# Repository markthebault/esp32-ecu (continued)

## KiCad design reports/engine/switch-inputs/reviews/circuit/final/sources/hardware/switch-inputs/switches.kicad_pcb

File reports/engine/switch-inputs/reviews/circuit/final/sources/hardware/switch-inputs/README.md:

# SW2-J4-DRAFT1 switch accessory

Separate80×60mm, two-layer, direct-solder THT prototype for two secondary-table dry contacts. The120×120mm carrier, service buttons, SAFE_N and archived manufacturing/case files retain their existing roles. **HOLD: no fabrication release, electrical rating, enclosure-fit or engine qualification.**

[Native schematic](switches.kicad_sch), [routed PCB](switches.kicad_pcb), [literal contract](net_contract.json) and [candidate BOM](bom.csv) describe42 footprints:38 fitted parts and four unplated M3 mounts. U1 is a directly soldered MCP23008-E/P PDIP18, without a socket. Ordinary resistors stand upright; confirm formed-lead and body heights before assembly. Exact capacitors, contact parts, wire/glands, mounting materials and some procurement choices remain open.

## Connections and ownership

| Carrier J4 | Accessory J1, XH4 | Signal |
| --- | --- | --- |
|1|1|GND|
|2|2|3V3|
|3|3|SDA, GPIO41|
|4|4|SCL, GPIO42|
|5|No wire or contact|SAFE_N, never connect to this accessory|

J4 is an internal3.3V logic header. Use a short internal harness with a five-position carrier housing and only positions1..4 populated, adapting to J1’s XH4 housing. The exact2.54mm carrier housing/contact and retention must be checked against the actual header. No loose fifth lead is permitted. J1 uses XHP-4 and four SXH-001T-P0.6 contacts as candidates; wire gauge/crimp tooling and fit need checking.

External J2 and J3 are VH2 connectors with3.96mm pitch, deliberately different from internal J1’s2.50mm XH4. Each VH2 uses pin1 SW and pin2 its ground return; J2 is input0 and J3 input1. VHR-2N housings and four SVH-21T-P1.1 contacts are candidates, with wire/crimp/retention checks pending. Keep these connectors inside the box and route each external pair through an appropriately selected sealed cable exit. No new sealed-box or printed-fit qualification is implied. Use dry-circuit rated switch contacts for the small sensing current.

A contact closes SW to its dedicated return. **Closed reads high, open reads low**, after transistor inversion. Selection polarity remains configurable per rule. An open wire looks open; a short to return looks closed. Static external voltage faults may also look like valid contact states. No continuity or wrong-wire diagnosis is implemented.

Saving a secondary rule in Input mode explicitly reserves J4’s bus and address0x20 for this fixed accessory contract. Connect no other I2C owner/device there. The marker/loop checks establish behavior, not unique identity. With neither rule in Input mode the firmware makes no device/register requests and releases its owned peripheral handles. PAIR, RESET, cam, pressure and SAFE_N retain their existing functions.

## Circuit and bounds

Each channel uses a1N4148 feed diode and2.2k0.6W1% bias, two4.99k1% base resistors,100k base-emitter bias, a reverse-BE1N4148 clamp, onsemi2N3904BU,4.7k collector pullup,10nF filtering and1k isolation to GP0/GP1. Do not substitute a transistor with another E/B/C bondout. GP2..5 have10k straps for0x28 under mask0x3C. GP7 is output-only on MCP23008; it drives GP6 through1k, with100k GP6 pulldown. These resistors limit contention if a register changes; they do not diagnose every contact failure.

MCP121-300E/TO is the prototype reset supervisor, with100k pullup matching its published test condition, local100nF bypass and a mandatory1k rail bleeder. The static trip range is2.857..3.003V; the stated80..180ms release interval has specified test conditions. Reset output leakage has no published maximum, hysteresis limits are at25°C, and assertion delay is typical only. The assembled RESET high/low margins, arbitrary ramps, power interruption and behavior below the specified operating supply remain unqualified. No guaranteed deep-brownout assertion is inferred from a different output load.

The feed diodes do not eliminate backfeed. Transistor B-C junctions and I2C/input clamp paths can energize an unpowered local rail. The1k bleeder and100Ω SDA/SCL series resistors are part of the prototype, not proof of safe arbitrary power sequences. The carrier already has4.7k I2C pullups; add no further bus pullups. Use100kHz and measure actual rise time/capacitance, VOL and fault behavior with the finished harness. Digital marker/loop/readback checks do not validate the analog conditioners: wrong transistor orientation, clamp faults or external wiring may still produce plausible contact bits. Independently measure both channels’ voltages/currents before accepting their raw levels.

The carrier LD1117’s200mA figure is a provisional **total thermal target**, not available accessory headroom. Measure the complete carrier, ESP32/Wi-Fi peaks and accessory rail loading/temperature. The module5V pad21 is NC. [Existing USB power restrictions](../../docs/web-configuration.md) still apply: remove the unpowered module before USB power; never combine powered carrier3V3 and module USB. A removed USB-powered module cannot read carrier sensors/J4.

MCP23008’s E order code does not establish3.3V operation to125°C. The data sheet’s3.3V operating domain ends at85°C. No assembled temperature rating is established. MRS25 candidate order codes are derived from the manufacturer’s coding scheme;0.6W is P70 subject to film/ambient limits, not an unrestricted enclosure dissipation rating. Exact capacitor part/body/lead spacing and all supplier footprints require physical verification.

## Acquisition and debugging

The monitor requests one logical operation per nominal5ms iteration. Startup reads the static marker before writes, sets sequential mode, configures GP7 as output, then alternates loopback challenges. Each GPIO sample reads registers0..10 and separately rereads IODIR. Owned configuration, marker, OLAT, INTF and loopback must agree; historical INTCAP is intentionally unused. A reset before the final guard rejects. A later reset remains unobserved until the next acquisition or freshness limit.

The entire operation has a measured3ms acceptance budget in the controller’s GP-timer epoch. Each synchronous SDK transfer receives the floored remaining integer-ms timeout; the trailing guard cannot start with less than1ms remaining. Source time is acquisition start. Writes never refresh it. SDK allocation/removal and preemption have no hard3ms deadline guarantee; an elapsed overrun invalidates the sample. Actual scheduling and watchdog behavior require HIL measurement.

Bus absence/NACK/timeout, register/loop/marker mismatch, malformed replies, elapsed overrun and producer gaps invalidate required inputs. Recoverable faults back off100ms and stay latched until a completed control observation consumes that exact fault ID. Successful reads alone cannot hide a fault when the engine lock was busy. A new guarded sample and each rule’s qualification period are required after acknowledgement. Clock/state faults require an ECU restart and survive Off/Input changes. Both rules may share one sampled channel with independent polarity/debounce.

The Engine page shows acquisition phase, requested mask, current/last fault, exact decimal-string source times/counters, fault awaiting consumption, operation durations and SDK ownership/result. Per-rule qualification, pending transition, age, raw level and selection remain in the existing web/USB/MSL diagnostics. Host stimuli stay synthetic; absent hardware diagnostics stay unknown. This adds no new tune/runtime wire fields or controller identity.

Start a future bench test with outputs disconnected/inhibited and both rules Off. Check rails and J4 wiring before enabling Input. Confirm each contact’s open/closed raw level, selected polarity, debounce and fault recovery, then deliberately test absence/reset/stuck lines and source freshness. Measure protection currents, reset levels, power-off backfeed, supply loading/temperature, scheduling and USB/RF interactions. A passing software/CAD/model check does not replace these measurements.

## Reproduction and limits

`/usr/bin/python3 scripts/build_switch_inputs.py` creates a fresh draft and refuses to replace an existing board without `--replace-generated`. Routing uses `scripts/route_switch_inputs.py` with pinned Freerouting1.9.0 and analytics disabled. Native KiCad9 all-severity ERC/DRC, connectivity and schematic parity are separate checks. No Gerber, drill or enclosure release is supplied.

`tools/run_switch_circuit.py` runs95 conditional ngspice cases: assumed BJT gain/temperature/rail/contact combinations, steady±18V experiments, unpowered I2C backfeed and two transient step sizes. Powered bus pullups follow the carrier rail; disconnected-supply cases use3.3V bus, plus a separate3.63V bus-only case. Bus-feed and carrier3V3-feed currents are reported separately. Its generic transistor/diode/clamp/supervisor parameters are **not manufacturer models or physical guarantees**. The±18V experiment is not an input rating or automotive surge test. The model intentionally retains backfeed and continuity limitations. Independent component-corner arithmetic likewise does not certify saturation/cutoff outside the manufacturer’s stated test conditions.

Primary references: [MCP23008 DS20001919I](https://ww1.microchip.com/downloads/aemDocuments/documents/APID/ProductDocuments/DataSheets/MCP23008-and-MCP23008-Data-Sheet-DS20001919.pdf), [MCP121 DS20001906D](https://ww1.microchip.com/downloads/en/DeviceDoc/20001906D.pdf), [onsemi2N3904](https://www.onsemi.com/download/data-sheet/pdf/2n3904-d.pdf), [1N4148](https://www.vishay.com/docs/81857/1n4148.pdf) and [MRS25](https://www.vishay.com/docs/28724/mrs16m25.pdf). Footprint origins and omitted metadata are recorded in [provenance](footprint-provenance.json).

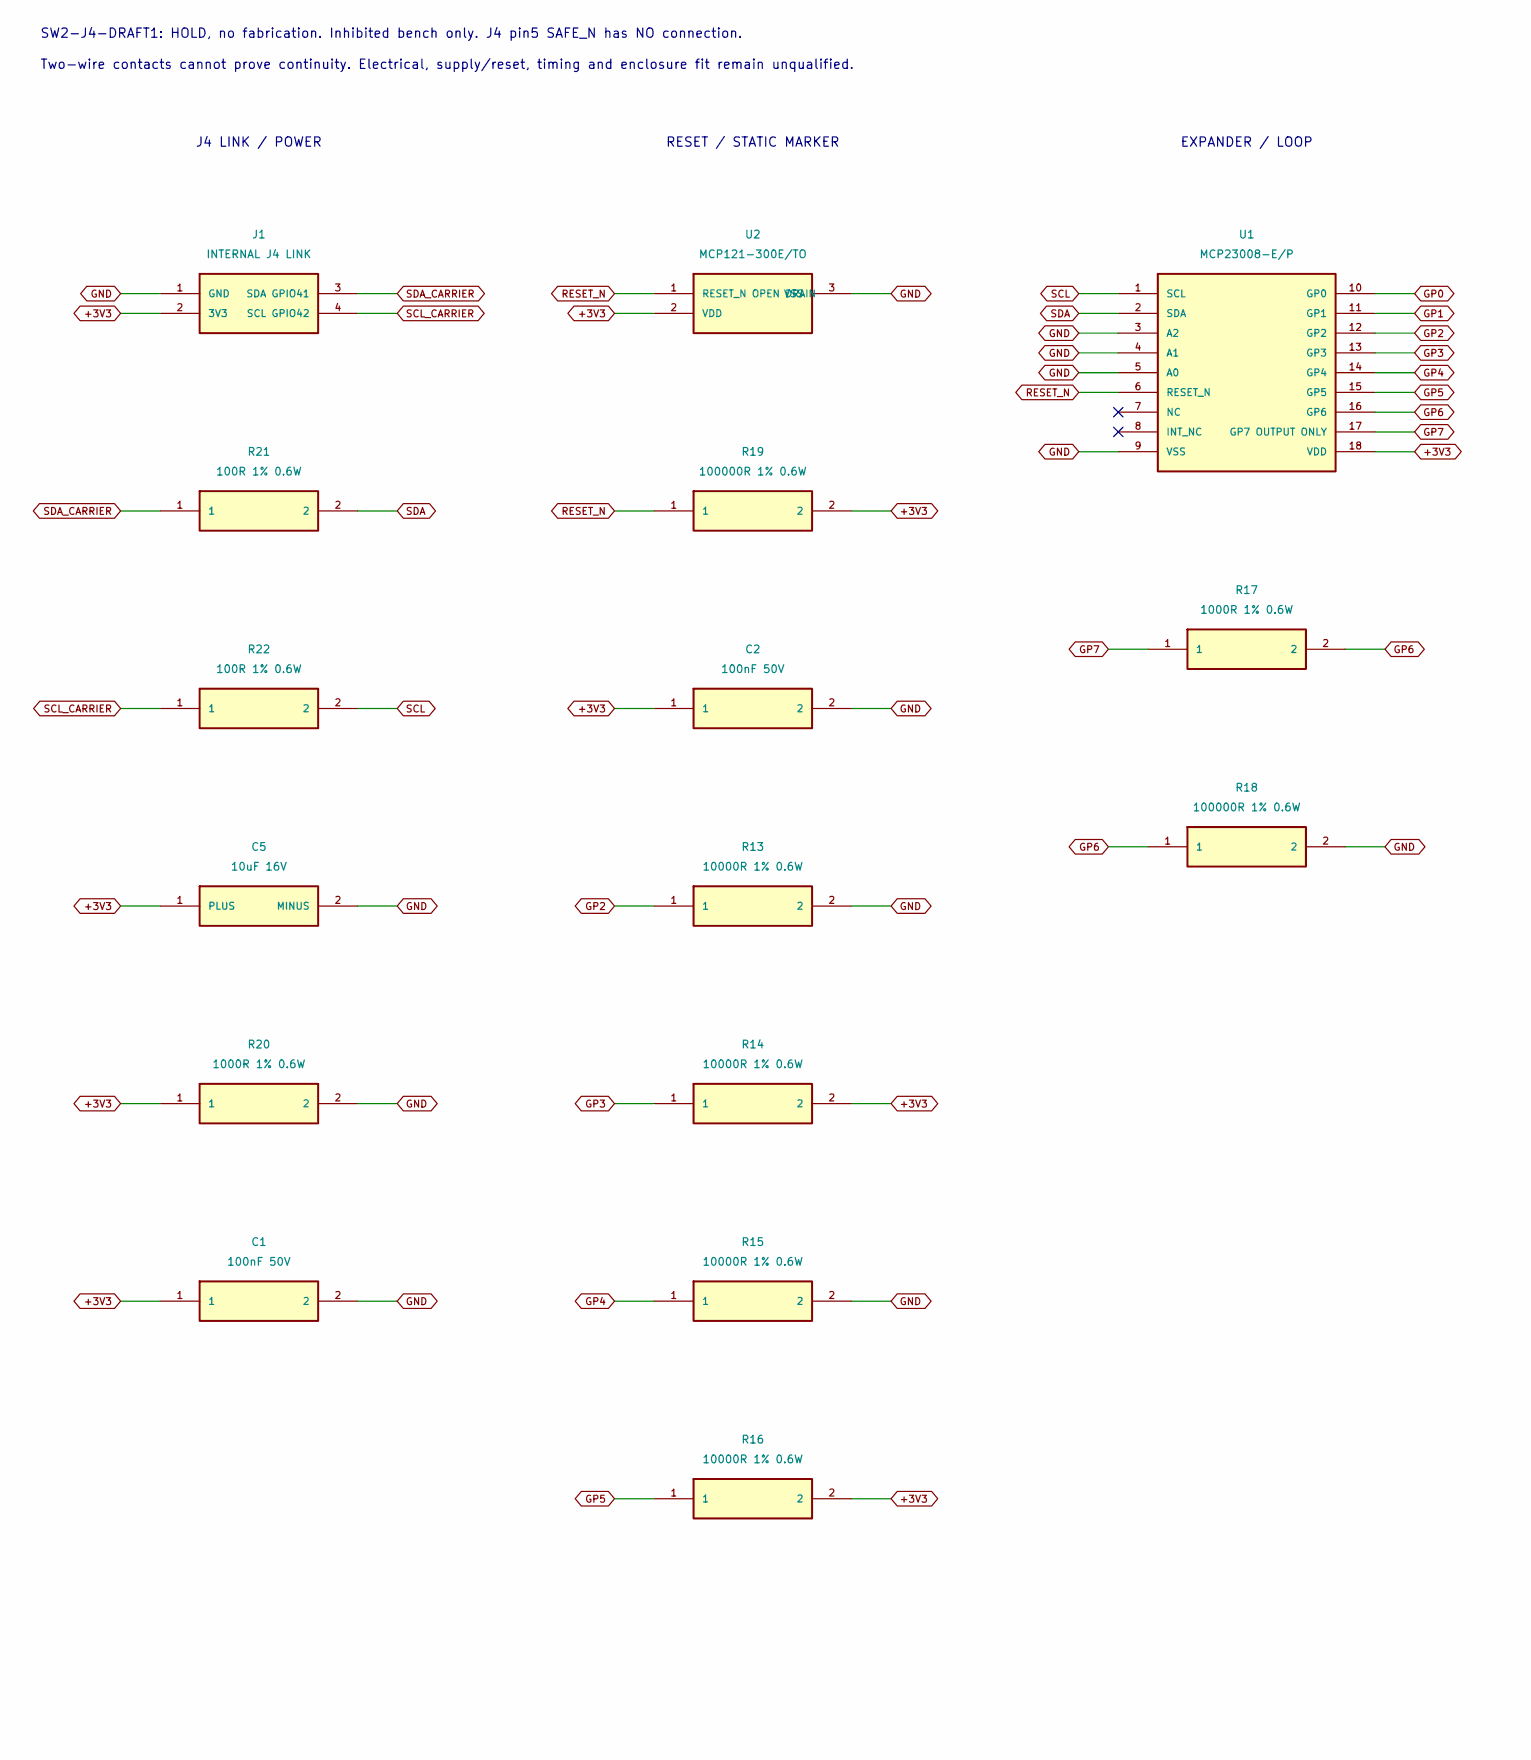
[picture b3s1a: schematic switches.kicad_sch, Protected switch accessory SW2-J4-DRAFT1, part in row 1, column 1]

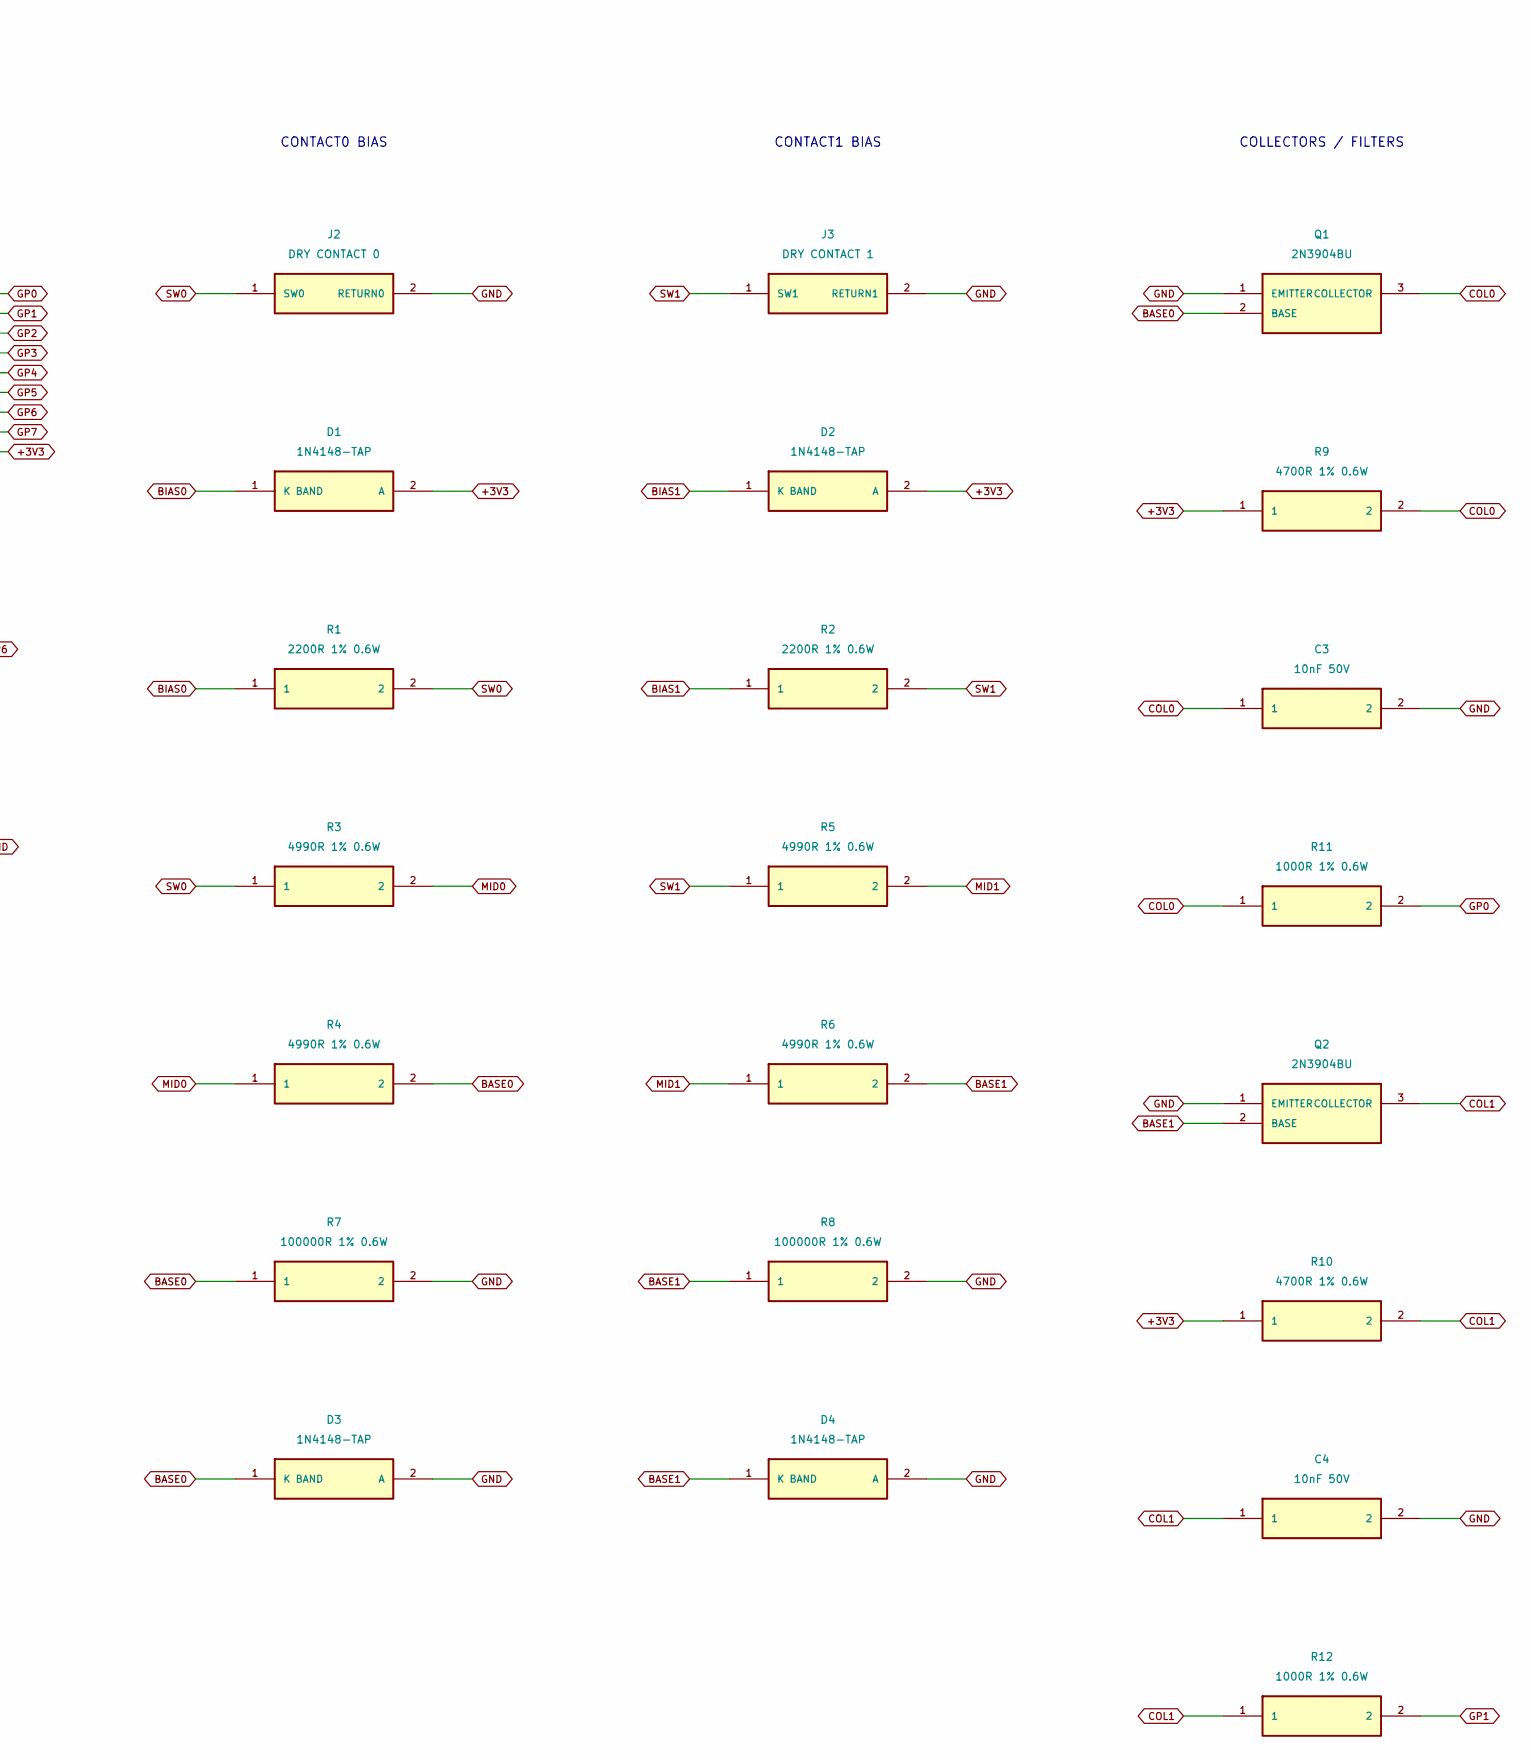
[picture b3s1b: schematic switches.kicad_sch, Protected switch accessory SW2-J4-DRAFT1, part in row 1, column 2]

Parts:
C1, C2: 100nF 50V; C_Disc_D5.0mm_W2.5mm_P5.00mm
C3, C4: 10nF 50V; C_Disc_D5.0mm_W2.5mm_P5.00mm
C5: 10uF 16V; CP_Radial_D8.0mm_P3.50mm
D1, D2, D3, D4: 1N4148-TAP; D_DO-35_SOD27_P3.81mm_Vertical_AnodeUp; MPN 1N4148-TAP
J1: INTERNAL J4 LINK; JST_XH_B4B-XH-A_1x04_P2.50mm_Vertical; MPN B4B-XH-A(LF)(SN)
J2: DRY CONTACT 0; JST_VH_B2P-VH_1x02_P3.96mm_Vertical; MPN B2P-VH(LF)(SN)
J3: DRY CONTACT 1; JST_VH_B2P-VH_1x02_P3.96mm_Vertical; MPN B2P-VH(LF)(SN)
Q1, Q2: 2N3904BU; TO-92_Inline_Wide; MPN 2N3904BU
R1, R2: 2200R 1% 0.6W; R_Axial_DIN0207_L6.3mm_D2.5mm_P2.54mm_Vertical; MPN MRS25000C2201FCT00
R3, R4, R5, R6: 4990R 1% 0.6W; R_Axial_DIN0207_L6.3mm_D2.5mm_P2.54mm_Vertical; MPN MRS25000C4991FCT00
R7, R8, R18, R19: 100000R 1% 0.6W; R_Axial_DIN0207_L6.3mm_D2.5mm_P2.54mm_Vertical; MPN MRS25000C1003FCT00
R9, R10: 4700R 1% 0.6W; R_Axial_DIN0207_L6.3mm_D2.5mm_P2.54mm_Vertical; MPN MRS25000C4701FCT00
R11, R12, R17, R20: 1000R 1% 0.6W; R_Axial_DIN0207_L6.3mm_D2.5mm_P2.54mm_Vertical; MPN MRS25000C1001FCT00
R13, R14, R15, R16: 10000R 1% 0.6W; R_Axial_DIN0207_L6.3mm_D2.5mm_P2.54mm_Vertical; MPN MRS25000C1002FCT00
R21, R22: 100R 1% 0.6W; R_Axial_DIN0207_L6.3mm_D2.5mm_P2.54mm_Vertical; MPN MRS25000C1000FCT00
U1: MCP23008-E/P; DIP-18_W7.62mm_LongPads; MPN MCP23008-E/P
U2: MCP121-300E/TO; TO-92_Inline_Wide; MPN MCP121-300E/TO

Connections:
+3V3: C1.1, C2.1, C5.1 (PLUS), D1.2 (A), D2.2 (A), J1.2 (3V3), R9.1, R10.1, R14.2, R16.2, R19.2, R20.1, U1.18 (VDD), U2.2 (VDD)
BASE0: D3.1 (K BAND), Q1.2 (BASE), R4.2, R7.1
BASE1: D4.1 (K BAND), Q2.2 (BASE), R6.2, R8.1
BIAS0: D1.1 (K BAND), R1.1
BIAS1: D2.1 (K BAND), R2.1
COL0: C3.1, Q1.3 (COLLECTOR), R9.2, R11.1
COL1: C4.1, Q2.3 (COLLECTOR), R10.2, R12.1
GND: C1.2, C2.2, C3.2, C4.2, C5.2 (MINUS), D3.2 (A), D4.2 (A), J1.1 (GND), J2.2 (RETURN0), J3.2 (RETURN1), Q1.1 (EMITTER), Q2.1 (EMITTER), R7.2, R8.2, R13.2, R15.2, R18.2, R20.2, U1.3 (A2), U1.4 (A1), U1.5 (A0), U1.9 (VSS), U2.3 (VSS)
GP0: R11.2, U1.10 (GP0)
GP1: R12.2, U1.11 (GP1)
GP2: R13.1, U1.12 (GP2)
GP3: R14.1, U1.13 (GP3)
GP4: R15.1, U1.14 (GP4)
GP5: R16.1, U1.15 (GP5)
GP6: R17.2, R18.1, U1.16 (GP6)
GP7: R17.1, U1.17 (GP7 OUTPUT ONLY)
MID0: R3.2, R4.1
MID1: R5.2, R6.1
RESET_N: R19.1, U1.6 (RESET_N), U2.1 (RESET_N OPEN DRAIN)
SCL: R22.2, U1.1 (SCL)
SCL_CARRIER: J1.4 (SCL GPIO42), R22.1
SDA: R21.2, U1.2 (SDA)
SDA_CARRIER: J1.3 (SDA GPIO41), R21.1
SW0: J2.1 (SW0), R1.2, R3.1
SW1: J3.1 (SW1), R2.2, R5.1

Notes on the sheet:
SW2-J4-DRAFT1: HOLD, no fabrication. Inhibited bench only. J4 pin5 SAFE_N has NO connection.
Two-wire contacts cannot prove continuity. Electrical, supply/reset, timing and enclosure fit remain unqualified.
J4 LINK / POWER
RESET / STATIC MARKER
EXPANDER / LOOP
CONTACT0 BIAS
CONTACT1 BIAS
COLLECTORS / FILTERS

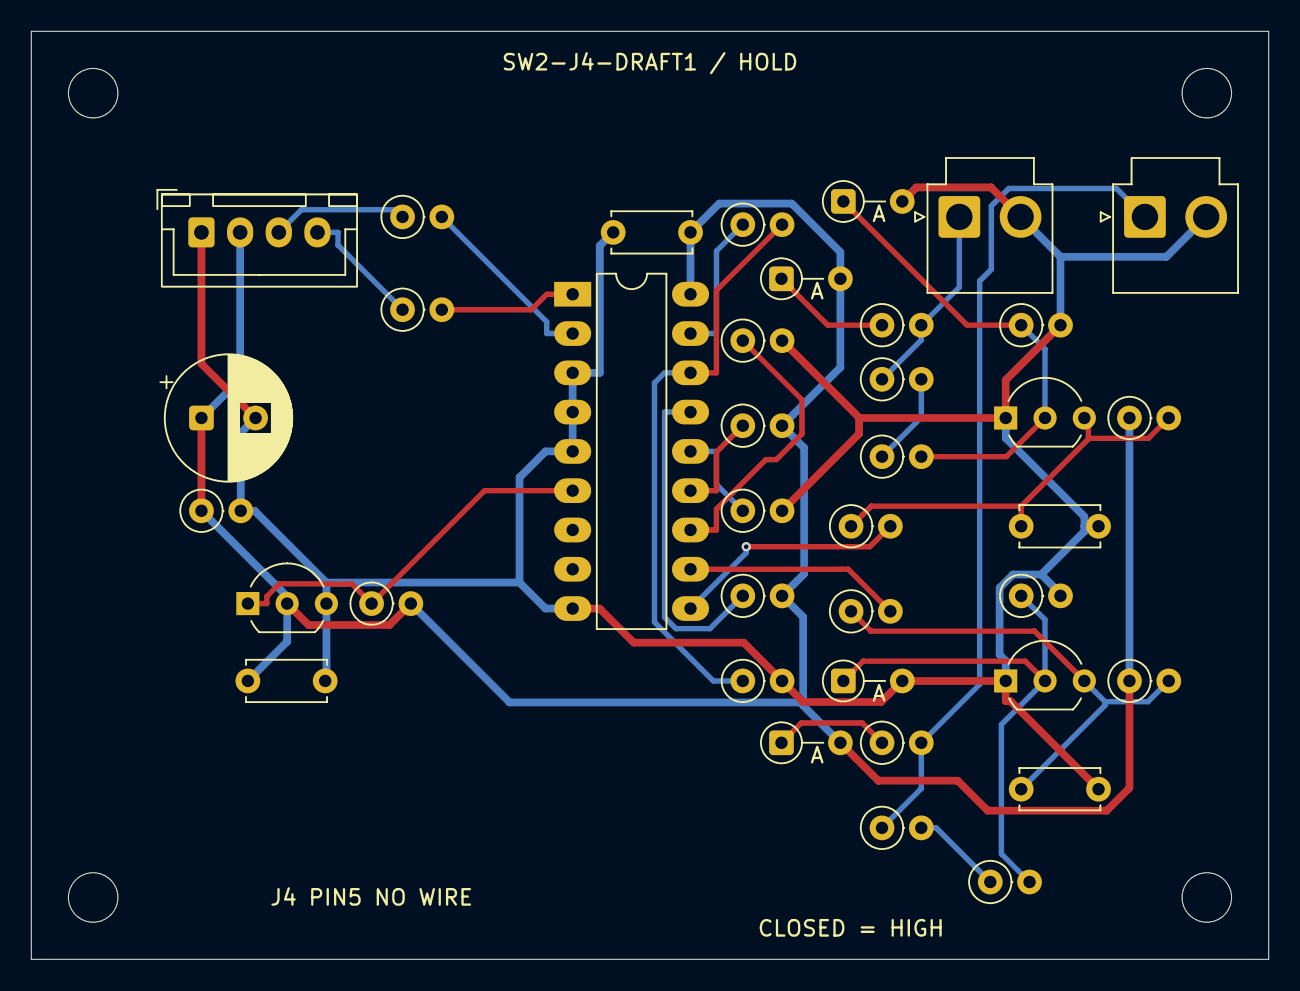
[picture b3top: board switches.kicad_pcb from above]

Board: 2 copper layers, 80.0 x 60.0 mm, 42 parts (0 on the bottom side), 25 nets.

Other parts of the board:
H1, H2, H3, H4: M3 INSULATED MOUNT; MountingHole_3.2mm_M3

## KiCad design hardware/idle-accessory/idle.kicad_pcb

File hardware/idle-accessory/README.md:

# Idle accessory placement and netlist draft

This is a separate 80 × 50 mm, two-layer, through-hole accessory with four M3 mounting holes on 72 × 42 mm centres. It preserves the A3/A4 carriers and manufacturing records. DIP 8 and TO220 devices solder directly; resistors stand upright. The copper is **unrouted**, with 28 connections outstanding. There are no manufacturing files or established case-fit dimensions for this accessory.

The [native KiCad project](idle.kicad_pro), [pin contract](net_contract.json), [BOM](bom.csv) and [footprint provenance](footprint-provenance.json) are review material. Native KiCad 9 checks give ERC 0, placement DRC 0 and schematic parity 0, plus the 28 unrouted connections. Those checks establish neither an electrically qualified board nor a printable or sealed fit.

| Connection | Pins / function |
| --- | --- |
| J1, four-pole XH | 1 GPIO3 from module socket pad 13; 2 hardware RUN_5V from TP6; 3 logic 5V from TP3; 4 ground from TP1 |
| J2, fixed screw terminal | 1 externally fused, switched, reverse/transient-protected actuator 12V; 2 dedicated actuator return |
| J3, two-pole VH | 1 valve positive; 2 IAC_LS |

J2 is a fixed [Phoenix Contact 1715721](https://www.phoenixcontact.com/en-us/products/printed-circuit-board-terminal-mkds-15-2-508-1715721) screw terminal. It cannot accept the J3 valve plug. Review found that identical supply/valve plugs would bypass the switch if exchanged, so the draft uses different connection systems. Terminal torque, wire retention and harness strain relief still require selection/testing.

The candidate chain is GPIO3 → 1 kΩ → [UCC27524P.B PDIP 8](https://www.ti.com/product/UCC27524/part-details/UCC27524P), then 220 Ω → [VNP35N07-E TO220](https://www.st.com/en/automotive-analog-and-power/vnp35n07-e.html). ENA receives hardware RUN_5V through 1 kΩ and has a mandatory 4.7 kΩ pull-down. INB and ENB are grounded; OUTB is unconnected. The switch input has 10 kΩ to source. Its metal tab is the live low-side drain. SB5H100 flyback has its cathode at valve positive and anode at IAC_LS. The 100 nF/1 µF capacitors decouple logic VDD. Exact leaded passive parts, insulation, thermal arrangement and valve remain procurement/qualification items.

The intended load is a two-wire, normally closed, energize-to-open continuous-duty PWM valve on a 9–16 V protected branch, bounded to 2 A. Neither the carrier's 1 A input branch nor its sensor/logic rails supply the valve. Software checks the existing board battery reading as a supply proxy; this draft has no valve-current, position or independent valve-supply feedback. Closing the command does not establish immediate mechanical closure.

**Physical release blockers remain:**

- GPIO3 is a JTAG strap. Read the actual module's eFuse routing without changing it. A permanent 2.2 kΩ carrier-side bias is required at the take-off; accessory R2 disappears when J1 is unplugged. The archived carrier has no new take-off connector or rework implemented.
- The draft joins logic and actuator grounds. If the J2 return opens, coil current can return through J1 and the carrier. Resolve isolation/return protection and verify that fault before powered integration.
- Route and review power/flyback loops and decoupling; specify the external fuse, relay/protection branch and actual valve; characterize current, decay, reset/backfeed and switch temperature. Mechanical mounting, antenna clearance, glands and sealing are unmeasured.

All shipped firmware environments keep idle GPIO writes compiled out. No configuration or UI option changes that policy. The selected N16R8 additionally rejects the experimental physical-idle flag. The draft is not ready for fabrication or powered valve testing.

Reproduce the generated draft only after inspecting local edits:

```sh
/usr/bin/python3 scripts/build_idle_accessory.py --replace-generated
kicad-cli sch erc hardware/idle-accessory/idle.kicad_sch --format json -o NEW_ERC.json
kicad-cli pcb drc hardware/idle-accessory/idle.kicad_pcb --schematic-parity --format json -o NEW_DRC.json
```

Only new footprint copies were adapted for the Linux KiCad 9 loader. The Mac KiCad 10 sources remain intact. The Phoenix terminal comes from a pinned official KiCad commit. Model paths are records, not a verified 3D assembly. See the [idle control guide](../../docs/engine-idle-control.md) for software, tuning and evidence.

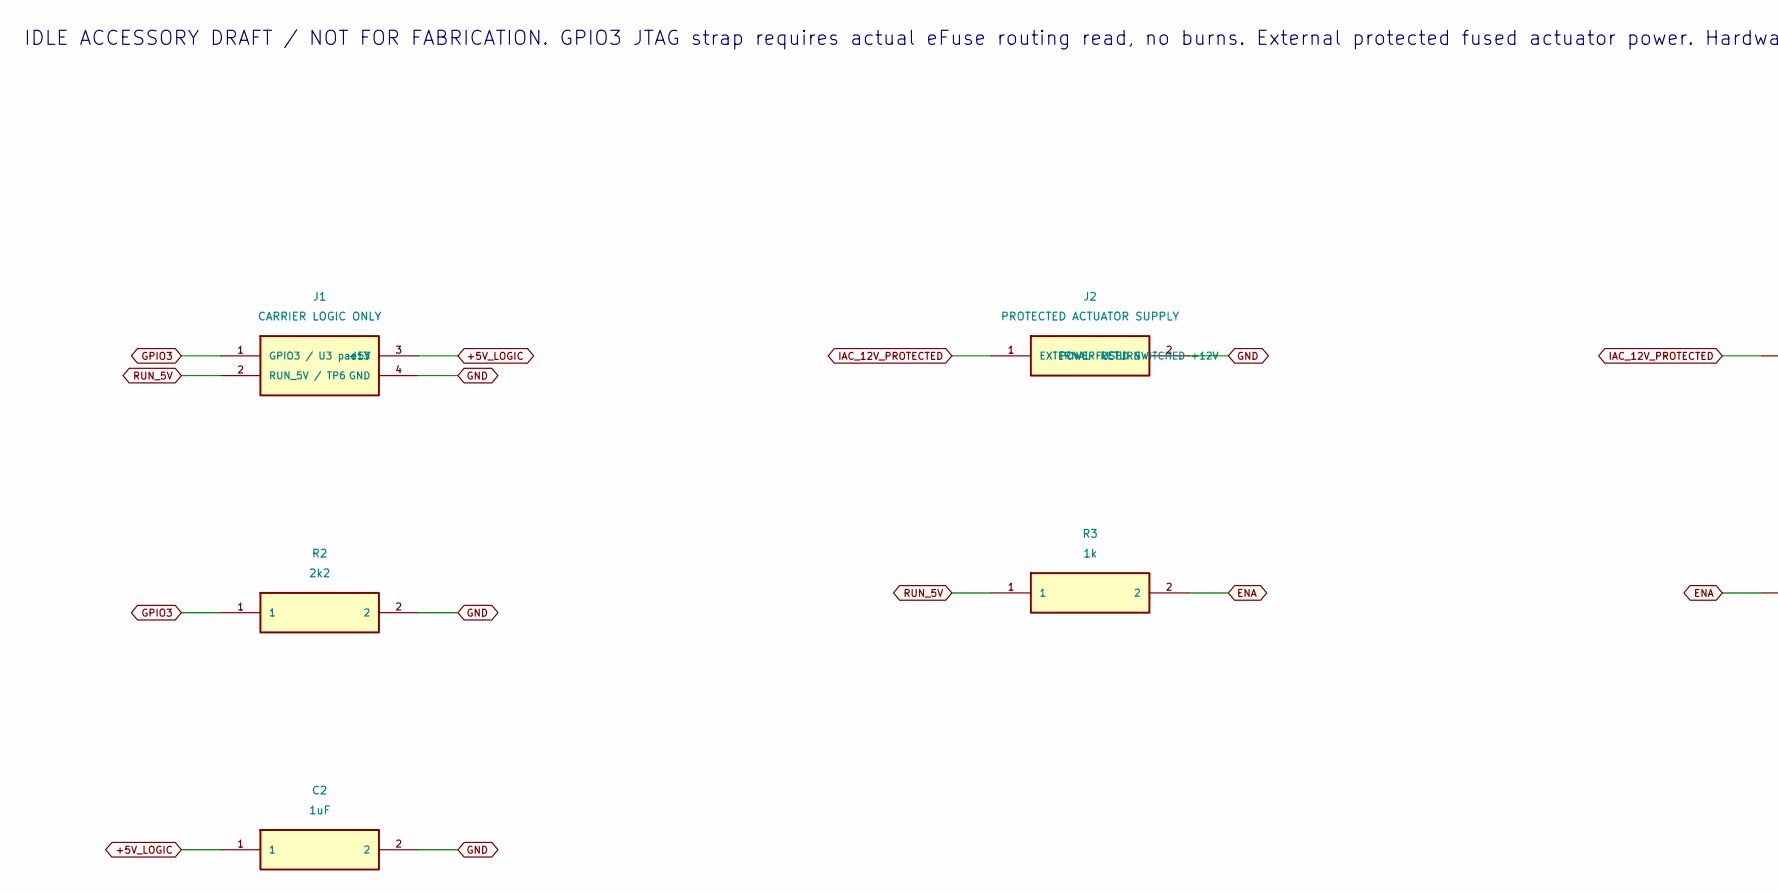
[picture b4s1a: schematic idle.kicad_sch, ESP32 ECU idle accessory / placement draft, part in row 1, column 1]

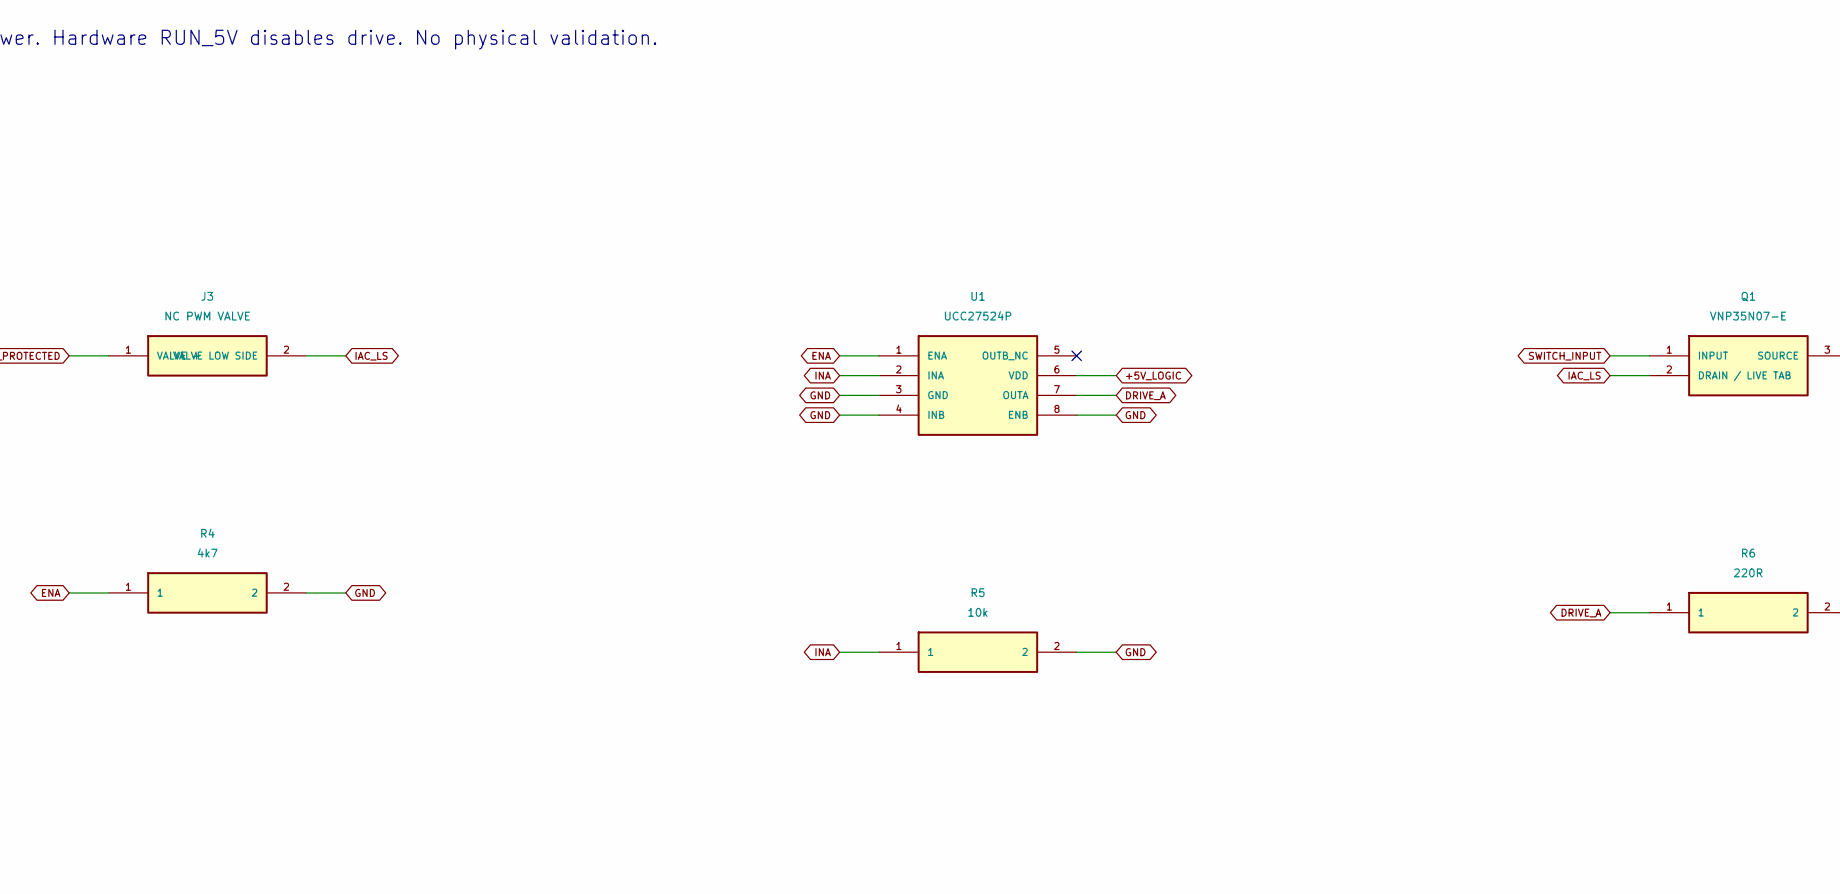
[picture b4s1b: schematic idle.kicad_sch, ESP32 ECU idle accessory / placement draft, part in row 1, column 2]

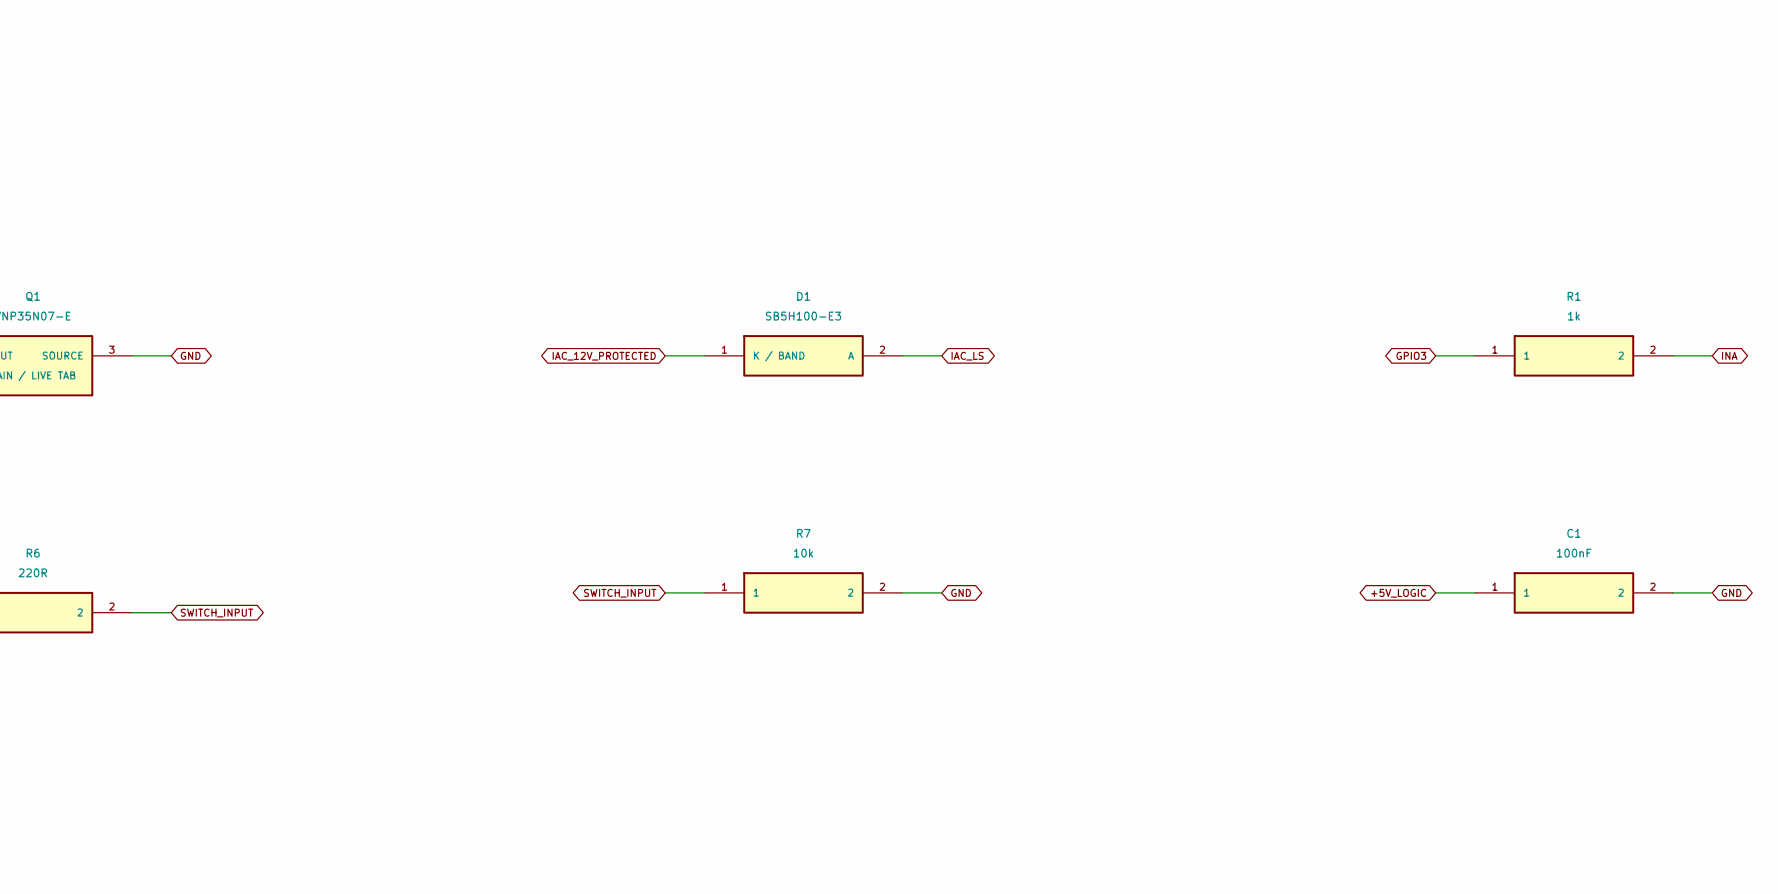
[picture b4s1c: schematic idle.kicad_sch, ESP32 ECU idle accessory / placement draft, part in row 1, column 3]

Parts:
C1: 100nF; C_Disc_D5.0mm_W2.5mm_P5.00mm
C2: 1uF; C_Rect_L7.2mm_W5.0mm_P5.00mm
D1: SB5H100-E3; D_DO-201AD_P15.24mm_Horizontal; MPN SB5H100-E3/54
J1: CARRIER LOGIC ONLY; JST_XH_B4B-XH-A_1x04_P2.50mm_Vertical; MPN B4B-XH-A(LF)(SN)
J2: PROTECTED ACTUATOR SUPPLY; TerminalBlock_Phoenix_MKDS-1,5-2-5.08_1x02_P5.08mm_Horizont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; MPN 1715721
J3: NC PWM VALVE; JST_VH_B2P-VH_1x02_P3.96mm_Vertical; MPN B2P-VH(LF)(SN)
Q1: VNP35N07-E; TO-220-3_Vertical; MPN VNP35N07-E
R1, R3: 1k; R_Axial_DIN0207_L6.3mm_D2.5mm_P2.54mm_Vertical
R2: 2k2; R_Axial_DIN0207_L6.3mm_D2.5mm_P2.54mm_Vertical
R4: 4k7; R_Axial_DIN0207_L6.3mm_D2.5mm_P2.54mm_Vertical
R5, R7: 10k; R_Axial_DIN0207_L6.3mm_D2.5mm_P2.54mm_Vertical
R6: 220R; R_Axial_DIN0207_L6.3mm_D2.5mm_P2.54mm_Vertical
U1: UCC27524P; DIP-8_W7.62mm_LongPads; MPN UCC27524P.B

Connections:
+5V_LOGIC: C1.1, C2.1, J1.3 (+5V), U1.6 (VDD)
DRIVE_A: R6.1, U1.7 (OUTA)
ENA: R3.2, R4.1, U1.1 (ENA)
GND: C1.2, C2.2, J1.4 (GND), J2.2 (POWER RETURN), Q1.3 (SOURCE), R2.2, R4.2, R5.2, R7.2, U1.3 (GND), U1.4 (INB), U1.8 (ENB)
GPIO3: J1.1 (GPIO3 / U3 pad13), R1.1, R2.1
IAC_12V_PROTECTED: D1.1 (K / BAND), J2.1 (EXTERNAL FUSED SWITCHED +12V), J3.1 (VALVE +)
IAC_LS: D1.2 (A), J3.2 (VALVE LOW SIDE), Q1.2 (DRAIN / LIVE TAB)
INA: R1.2, R5.1, U1.2 (INA)
RUN_5V: J1.2 (RUN_5V / TP6), R3.1
SWITCH_INPUT: Q1.1 (INPUT), R6.2, R7.1

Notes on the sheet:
IDLE ACCESSORY DRAFT / NOT FOR FABRICATION. GPIO3 JTAG strap requires actual eFuse routing read, no burns. External protected fused actuator power. Hardware RUN_5V disables drive. No physical validation.

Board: 2 copper layers, 19 parts (0 on the bottom side), 10 nets, no tracks yet.

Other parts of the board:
H1, H2, H3, H4: M3 MOUNT; MountingHole_3.2mm_M3

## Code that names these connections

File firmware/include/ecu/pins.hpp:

#pragma once
// Generated by scripts/build_hardware.py from scripts/design.py.
namespace ecu::pins {
inline constexpr int inj1_cmd = 4;
inline constexpr int inj2_cmd = 5;
inline constexpr int inj3_cmd = 6;
inline constexpr int inj4_cmd = 7;
inline constexpr int ign1_cmd = 15;
inline constexpr int ign2_cmd = 16;
inline constexpr int ign3_cmd = 17;
inline constexpr int ign4_cmd = 18;
inline constexpr int crank = 8;
inline constexpr int cam = 9;
inline constexpr int adc_cs = 10;
inline constexpr int spi_mosi = 11;
inline constexpr int spi_clk = 12;
inline constexpr int spi_miso = 13;
inline constexpr int can_tx = 14;
inline constexpr int can_rx = 21;
#if defined(ECU_HAND_SOLDER_A1) || defined(ECU_THROUGH_HOLE_A2) || defined(ECU_COMPACT_A3)
inline constexpr int arm = 47;
#else
inline constexpr int arm = 38;
#endif
inline constexpr int wdi = 39;
inline constexpr int safe_n_mon = 40;
inline constexpr int i2c_sda = 41;
inline constexpr int i2c_scl = 42;
inline constexpr int uart_tx = 43;
inline constexpr int uart_rx = 44;
inline constexpr int pump_cmd = 2;
inline constexpr int fan_cmd = 1;
inline constexpr int interlock = 48;
}

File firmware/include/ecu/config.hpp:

#pragma once
#include <array>
#include <cmath>
#include <cstdint>
#include <cstring>
namespace ecu::config {
constexpr unsigned kSensors=6, kPoints=16;
enum class Mode { Voltage, Linear, Table, Ntc };
struct Point { double v{}, value{}; };
struct Sensor {
 char id[16]{},label[64]{},unit[16]{};Mode mode{Mode::Voltage};bool confirmed{},pullup_fitted{};
 bool ratiometric{};double reference_supply_v{5};
 double fault_low_v{.02},fault_high_v{5.15},filter_ms{100},v0{.5},y0{},v1{4.5},y1{100};
 double ntc_r0_ohm{10000},ntc_t0_c{25},ntc_beta_k{3950},pullup_ohm{2490};
 unsigned point_count{2};std::array<Point,kPoints> points{};
};
struct Config {std::uint32_t revision{1};char name[64]{"ECU bench profile"};double adc_reference_v{3.3};unsigned ui_poll_ms{500},slots{60},missing{2},max_rpm{8000};std::array<Sensor,kSensors> sensors{};};
inline bool finite(double x){return std::isfinite(x);}
inline bool valid(const Config& c){
 if (!finite(c.adc_reference_v)||c.adc_reference_v<2.9||c.adc_reference_v>3.6||c.ui_poll_ms<100||c.ui_poll_ms>2000||c.slots<12||c.slots>120||c.missing<1||c.missing>3||c.missing>=c.slots/4||c.max_rpm<500||c.max_rpm>12000)return false;
 const char* ids[]={"map","tps","clt","iat","wideband","postcat"};
 for(unsigned i=0;i<kSensors;++i){const auto&s=c.sensors[i];
  if(std::strcmp(s.id,ids[i])||!s.label[0]||!s.unit[0]||!finite(s.fault_low_v)||!finite(s.fault_high_v)||s.fault_low_v<0||s.fault_high_v>5.3||s.fault_low_v>=s.fault_high_v||!finite(s.filter_ms)||s.filter_ms<0||s.filter_ms>2000)return false;
  if(!finite(s.v0)||!finite(s.v1)||s.v0<0||s.v1>5.3||s.v1-s.v0<.01||!finite(s.y0)||!finite(s.y1)||std::abs(s.y0)>100000||std::abs(s.y1)>100000)return false;
  if(s.point_count<2||s.point_count>kPoints)return false;
  for(unsigned p=0;p<s.point_count;++p)if(!finite(s.points[p].v)||!finite(s.points[p].value)||s.points[p].v<0||s.points[p].v>5.3||std::abs(s.points[p].value)>100000||(p&&s.points[p].v-s.points[p-1].v<.001))return false;
  if(!finite(s.ntc_r0_ohm)||s.ntc_r0_ohm<100||s.ntc_r0_ohm>1000000||!finite(s.ntc_t0_c)||s.ntc_t0_c< -50||s.ntc_t0_c>150||!finite(s.ntc_beta_k)||s.ntc_beta_k<1000||s.ntc_beta_k>10000||!finite(s.pullup_ohm)||s.pullup_ohm<100||s.pullup_ohm>100000)return false;
  if(s.mode==Mode::Ntc&&(!(i==2||i==3)||!s.pullup_fitted))return false;
  if(!finite(s.reference_supply_v)||s.reference_supply_v<4||s.reference_supply_v>5.3||
     (s.ratiometric&&s.mode!=Mode::Linear&&s.mode!=Mode::Table))return false;
 }
 return true;
}
// Readout filters use this voltage basis. Ratiometric samples are normalized
// before filtering, while the engine continues using instantaneous readings.
inline double transfer_voltage(const Sensor&s,double sensor_v,double supply){
 if(!s.ratiometric)return sensor_v;
 if((s.mode!=Mode::Linear&&s.mode!=Mode::Table)||!finite(s.reference_supply_v)||
    s.reference_supply_v<4||s.reference_supply_v>5.3||!finite(supply)||supply<4||supply>5.3)return NAN;
 return sensor_v*s.reference_supply_v/supply;
}
inline double readout_filter(const Sensor&s,double sensor_v,double supply,double previous,
                             double dt_ms,bool reset,bool adc_ok=true){
 if(s.ratiometric&&!adc_ok)return NAN;
 const double v=transfer_voltage(s,sensor_v,supply);
 if(!finite(v))return NAN;
 if(reset||s.filter_ms<=0||!finite(previous))return v;
 return previous+dt_ms/(s.filter_ms+dt_ms)*(v-previous);
}
struct Reading {double value{},sensor_v{},adc_v{},transfer_v{NAN};bool valid{};const char* fault{"waiting"};};
inline Reading convert(const Sensor&s,double sensor_v,double adc_v,double supply,const double*filtered_transfer=nullptr){
 Reading r{};r.sensor_v=sensor_v;r.adc_v=adc_v;r.transfer_v=transfer_voltage(s,sensor_v,supply);
 if(!finite(sensor_v)||!finite(adc_v)){r.fault="invalid sample";return r;}
 if(sensor_v<s.fault_low_v){r.fault="below input range";return r;}if(sensor_v>s.fault_high_v){r.fault="above input range";return r;}
 if(s.ratiometric&&!finite(r.transfer_v)){r.fault="ratiometric supply or configuration invalid";return r;}
 if(s.ratiometric&&filtered_transfer)r.transfer_v=*filtered_transfer;
 if(!finite(r.transfer_v)){r.fault="conversion voltage unavailable";return r;}
 const double input_v=r.transfer_v;
 if(s.mode==Mode::Voltage)r.value=sensor_v;
 else if(s.mode==Mode::Linear){if(input_v<s.v0||input_v>s.v1){r.fault="outside calibration";return r;}r.value=s.y0+(input_v-s.v0)*(s.y1-s.y0)/(s.v1-s.v0);}
 else if(s.mode==Mode::Table){
  if(input_v<s.points[0].v||input_v>s.points[s.point_count-1].v){r.fault="outside calibration";return r;}
  unsigned p=1;while(p<s.point_count-1&&input_v>s.points[p].v)++p;
  const auto&a=s.points[p-1];const auto&b=s.points[p];r.value=a.value+(input_v-a.v)*(b.value-a.value)/(b.v-a.v);
 }else{
  if(!s.pullup_fitted){r.fault="pull-up not confirmed";return r;}
  if(!finite(supply)||supply<4||supply>5.3||sensor_v<=.001||sensor_v>=supply){r.fault="supply / NTC wiring";return r;}
  const double req=s.pullup_ohm*sensor_v/(supply-sensor_v);
  const double inv=1/req-1/55000.0; // The board's 22k + 33k divider loads the sensor.
  if(inv<=0){r.fault="NTC open / wrong pull-up";return r;}
  const double resistance=1/inv, kelvin=1/(1/(s.ntc_t0_c+273.15)+std::log(resistance/s.ntc_r0_ohm)/s.ntc_beta_k);
  r.value=kelvin-273.15;
  if(!finite(r.value)||r.value< -80||r.value>250){r.fault="NTC curve / open circuit";return r;}
 }
 r.valid=finite(r.value);r.fault=r.valid?"ok":"invalid conversion";return r;
}
}
